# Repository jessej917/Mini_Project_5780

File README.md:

# Mini_Project_5780
 ECE 5780 Project

Authors:
Jesse Jenkins
Israel Prescott
Jacob Metcalf

Files:
 - Balancing_Robot_MiniProject(Code)
 - Documentation(Explaining the Project)
 - PCB Design(Used Teachers PCB Design)
 -Self_Balancing_Robot_CAD(CAD Designs)

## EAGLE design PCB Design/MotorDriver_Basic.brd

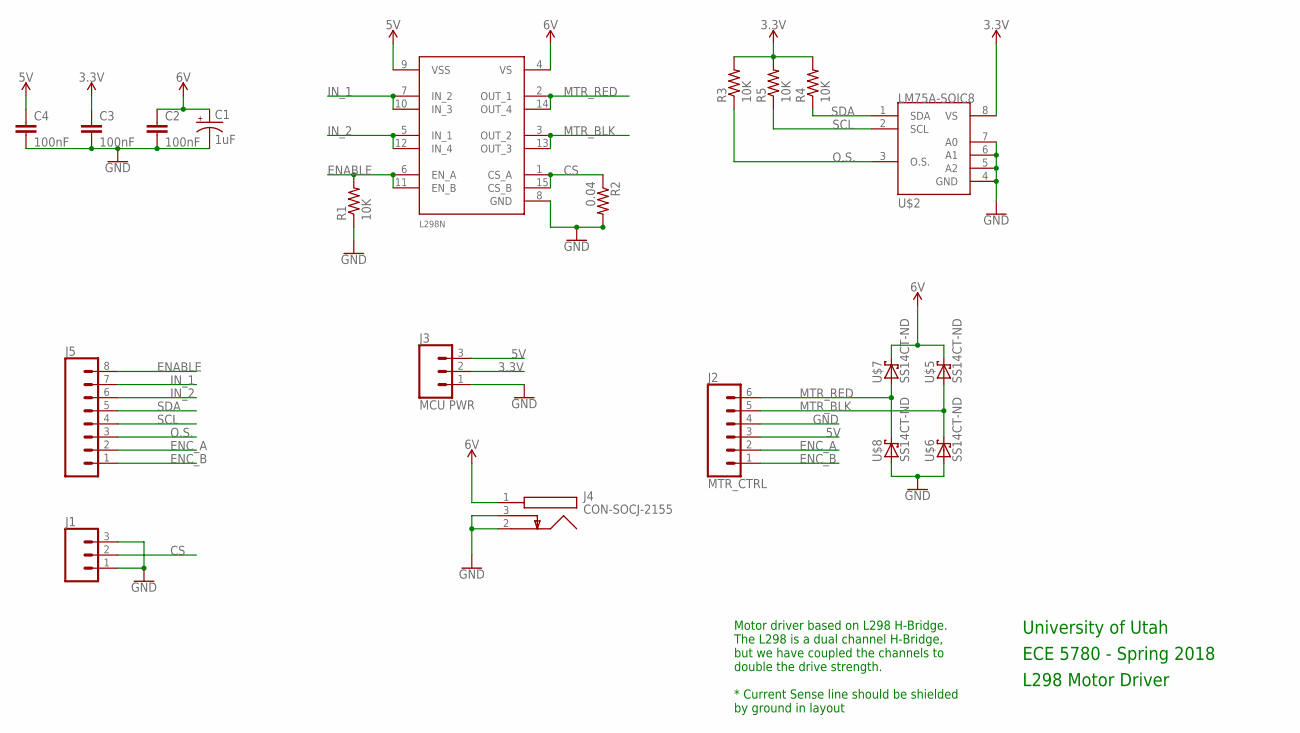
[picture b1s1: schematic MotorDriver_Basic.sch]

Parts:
C1: 1uF; E2,5-6
C2, C3, C4: 100nF; C1206
J1: CONN_03; 1X03
J2: MTR_CTRL; 1X06
J3: MCU PWR; 1X03
J4: CON-SOCJ-2155; CONSOCJ2155
J5: CONN_08"; 1X08
L298N: L298N-MULTIWATT15
R1, R3, R4, R5: 10K; M1206
R2: 0.04; M1206
U$2: LM75A-SOIC8; SOIC-8
U$5, U$6, U$7, U$8: SS14CT-ND; SOD106A-W

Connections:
3.3V: C3.1, J3.2, R3.2, R4.2, R5.2, U$2.8 (VS)
5V: C4.1, J2.3, J3.3, L298N.9 (VSS)
CS: J1.2, L298N.1 (CS_A), L298N.15 (CS_B), R2.1
ENABLE: J5.8, L298N.6 (EN_A), L298N.11 (EN_B), R1.2
ENC_A: J2.2, J5.2
ENC_B: J2.1, J5.1
GND: C1.-, C2.2, C3.2, C4.2, J1.1, J1.3, J2.4, J3.1, J4.2, J4.3, L298N.8 (GND), R1.1, R2.2, U$2.4 (GND), U$2.5 (A2), U$2.6 (A1), U$2.7 (A0), U$6.A, U$8.A
IN_1: J5.7, L298N.7 (IN_2), L298N.10 (IN_3)
IN_2: J5.6, L298N.5 (IN_1), L298N.12 (IN_4)
MTR_BLK: J2.5, L298N.3 (OUT_2), L298N.13 (OUT_3), U$5.A, U$6.C
MTR_RED: J2.6, L298N.2 (OUT_1), L298N.14 (OUT_4), U$7.A, U$8.C
O.S.: J5.3, R3.1, U$2.3 (O.S.)
SCL: J5.4, R5.1, U$2.2 (SCL)
SDA: J5.5, R4.1, U$2.1 (SDA)
VCC: C1.+, C2.1, J4.1, L298N.4 (VS), U$5.C, U$7.C

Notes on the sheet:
University of Utah
ECE 5780 - Spring 2018
L298 Motor Driver
Motor driver based on L298 H-Bridge. The L298 is a dual channel H-Bridge, but we have coupled the channels to double the drive strength. * Current Sense line should be shielded by ground in layout

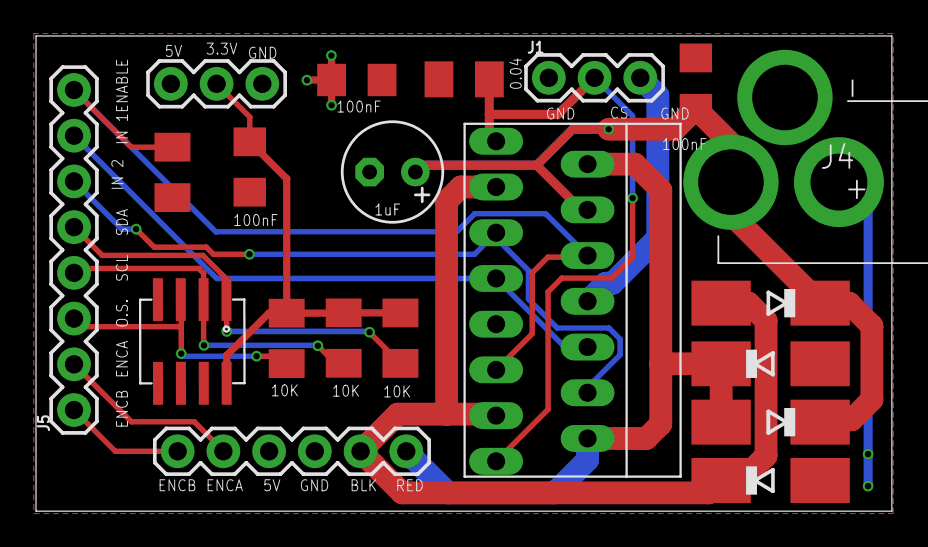
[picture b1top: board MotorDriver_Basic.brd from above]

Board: 2 copper layers, 47.5 x 26.4 mm, 20 parts (0 on the bottom side), 15 nets.

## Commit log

2024-03-21 Added My Name
2024-03-21 Added Israel Prescott to Authors
2024-04-03 Created Project
2024-04-04 Wrapped Gyroscope with Motor Controller
2024-04-04 Changed Error to gyroscope's angle
2024-04-04 Fine tuned base axis variables
2024-04-10 Moved to y axis
2024-04-18 Fixed backwards stopping
2024-04-25 Submitted Final
2024-04-26 Live demo of robot balancing
2024-04-27 Added the Documentation and PCB Design
2024-04-27 CAD
    Addded CAD files for Robot.
2024-04-27 Updated Documentation

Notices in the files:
parts and their libraries:
SparkFun-Connectors: Licensing: Creative Commons ShareAlike 4.0 International - https://creativecommons.org/licenses/by-sa/4.0
